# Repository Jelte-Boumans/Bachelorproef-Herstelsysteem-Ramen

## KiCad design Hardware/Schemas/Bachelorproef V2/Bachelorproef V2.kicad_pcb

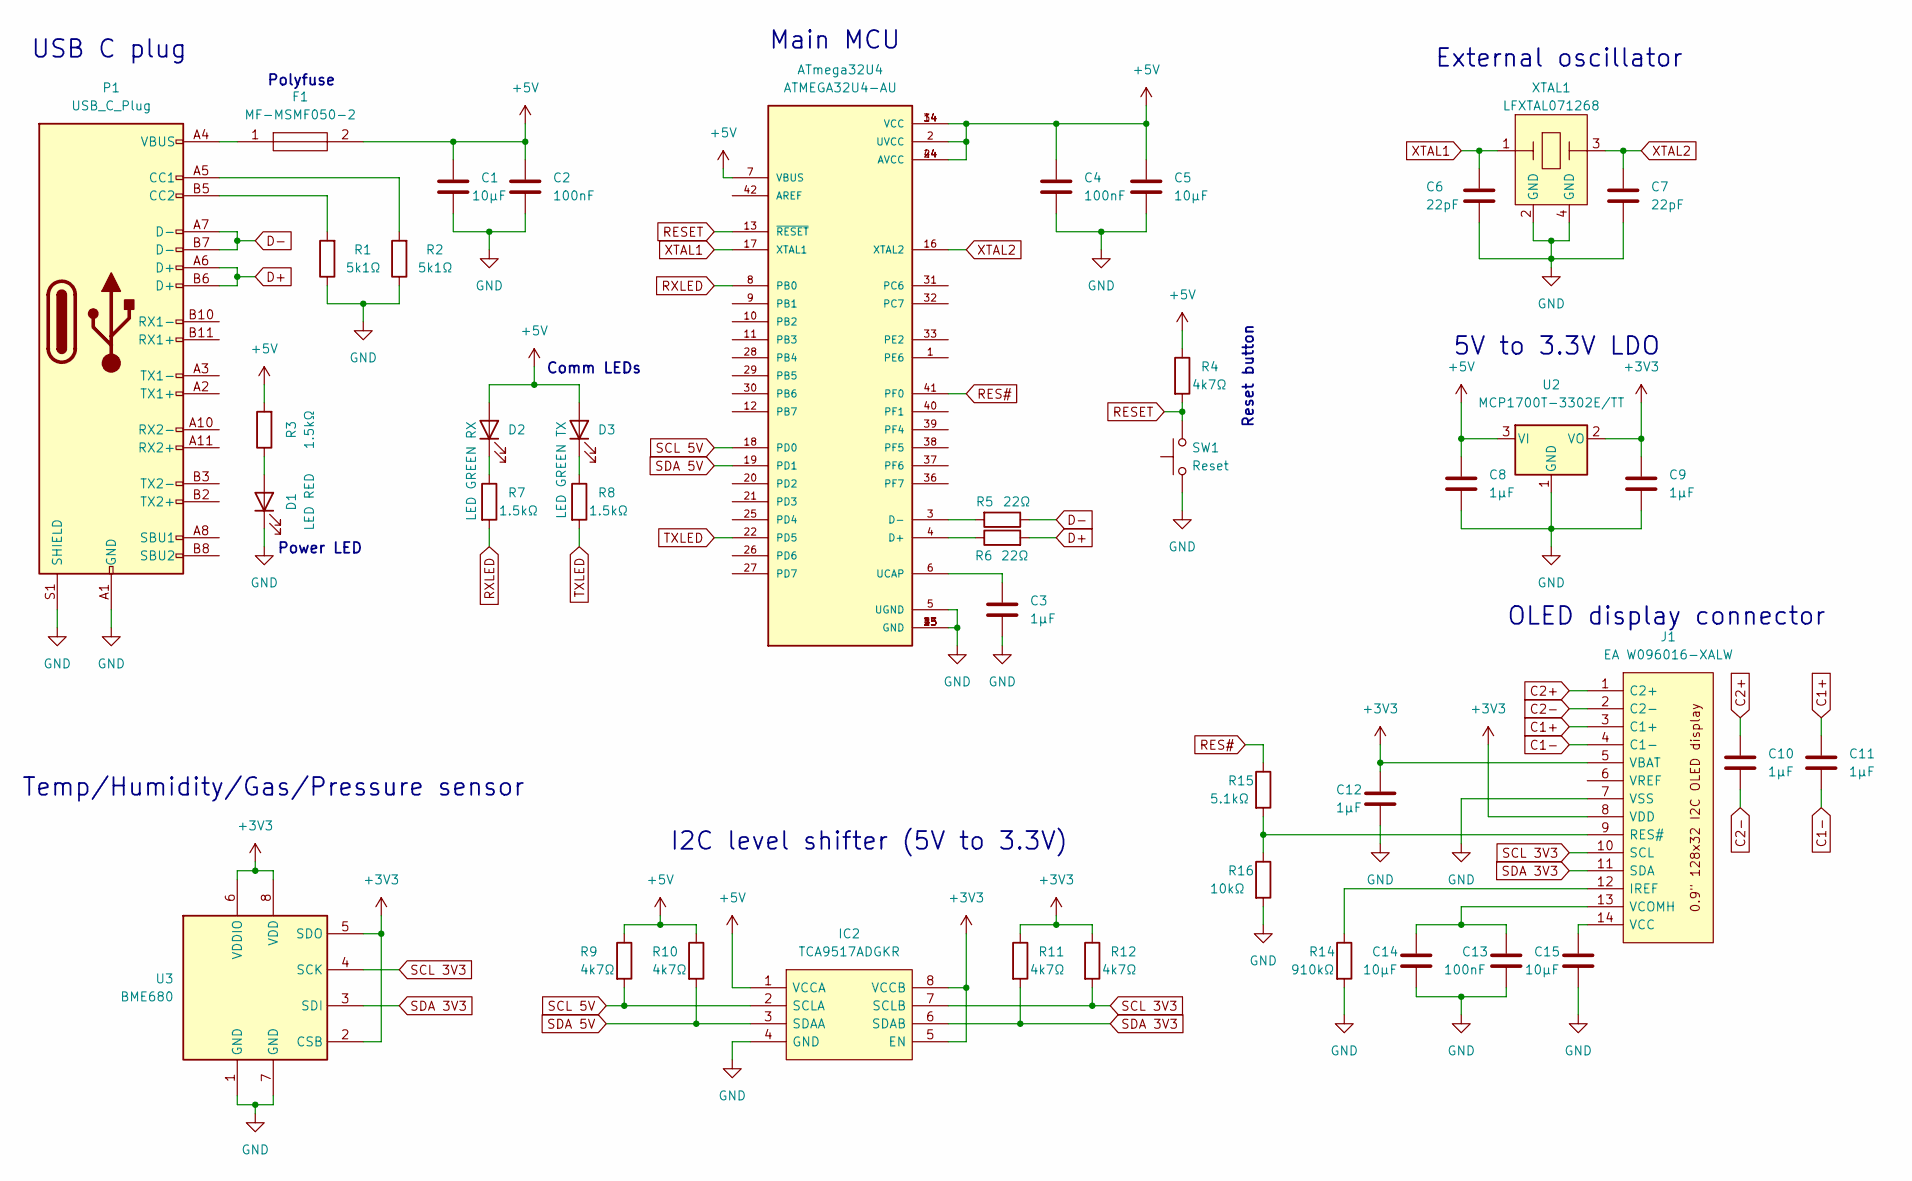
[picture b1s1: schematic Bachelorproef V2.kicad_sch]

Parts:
ATmega32U4: ATMEGA32U4-AU
C1, C5, C14, C15: 10µF; C_0603_1608Metric
C2, C4, C13: 100nF; C_0603_1608Metric
C3, C8, C9, C10, C11, C12: 1µF; C_0603_1608Metric
C6, C7: 22pF; C_0603_1608Metric
D1: LED RED; LED_0603_1608Metric_Pad1.05x0.95mm_HandSolder
D2: LED GREEN RX; LED_0603_1608Metric_Pad1.05x0.95mm_HandSolder
D3: LED GREEN TX; LED_0603_1608Metric_Pad1.05x0.95mm_HandSolder
F1: MF-MSMF050-2; Mouser Part Number 652-MF-MSMF050-2
IC2: TCA9517ADGKR
J1: EA W096016-XALW; EA_W096016-XALW
P1: USB_C_Plug; CX60-24S-UNIT
R1, R2: 5k1Ω; R_0603_1608Metric_Pad0.98x0.95mm_HandSolder
R3, R7, R8: 1.5kΩ; R_0603_1608Metric_Pad0.98x0.95mm_HandSolder
R4, R9, R10, R11, R12: 4k7Ω; R_0603_1608Metric_Pad0.98x0.95mm_HandSolder
R5, R6: 22Ω; R_0603_1608Metric_Pad0.98x0.95mm_HandSolder
R14: 910kΩ; R_0603_1608Metric_Pad0.98x0.95mm_HandSolder
R15: 5.1kΩ; R_0603_1608Metric_Pad0.98x0.95mm_HandSolder
R16: 10kΩ; R_0603_1608Metric_Pad0.98x0.95mm_HandSolder
SW1: Reset; SW_PTS636_SM43J_SMTR_LFS
U2: MCP1700T-3302E/TT; SOT-23
U3: BME680; Bosch_LGA-8_3x3mm_P0.8mm_ClockwisePinNumbering
XTAL1: LFXTAL071268

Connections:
+3V3: C9.1, C12.1, IC2.5 (EN), IC2.8 (VCCB), J1.5 (VBAT), J1.8 (VDD), R11.1, R12.1, U2.2 (VO), U3.2 (CSB), U3.5 (SDO), U3.6 (VDDIO), U3.8 (VDD)
+5V: ATmega32U4.2 (UVCC), ATmega32U4.7 (VBUS), ATmega32U4.14 (VCC), ATmega32U4.24 (AVCC), ATmega32U4.34 (VCC), ATmega32U4.44 (AVCC), C1.1, C2.1, C4.1, C5.1, C8.1, D2.2 (A), D3.2 (A), F1.2, IC2.1 (VCCA), R3.2, R4.1, R9.1, R10.1, U2.3 (VI)
C1+: C11.1, J1.3 (C1+)
C1-: C11.2, J1.4 (C1-)
C2+: C10.1, J1.1 (C2+)
C2-: C10.2, J1.2 (C2-)
D+: P1.A6 (D+), P1.B6 (D+), R6.2
D-: P1.A7 (D-), P1.B7 (D-), R5.1
GND: ATmega32U4.5 (UGND), ATmega32U4.15 (GND), ATmega32U4.23 (GND), ATmega32U4.35 (GND), ATmega32U4.43 (GND), C1.2, C2.2, C3.2, C4.2, C5.2, C6.2, C7.2, C8.2, C9.2, C12.2, C13.2, C14.2, C15.2, D1.1 (K), IC2.4 (GND), J1.7 (VSS), P1.A1 (GND), P1.A12 (GND), P1.B1 (GND), P1.B12 (GND), P1.S1 (SHIELD), R1.1, R2.1, R14.2, R16.2, SW1.1, U2.1 (GND), U3.1 (GND), U3.7 (GND), XTAL1.2 (GND), XTAL1.4 (GND)
unnamed: ATmega32U4.6 (UCAP), C3.1
unnamed: C13.1, C14.1, J1.13 (VCOMH)
unnamed: C15.1, J1.14 (VCC)
unnamed: D1.2 (A), R3.1
unnamed: D2.1 (K), R7.1
unnamed: D3.1 (K), R8.1
unnamed: F1.1, P1.A4 (VBUS), P1.A9 (VBUS), P1.B4 (VBUS), P1.B9 (VBUS)
unnamed: J1.9 (RES#), R15.2, R16.1
unnamed: J1.12 (IREF), R14.1
unnamed: P1.A5 (CC1), R2.2
unnamed: P1.B5 (CC2), R1.2
unnamed: ATmega32U4.3 (D-), R5.2
unnamed: ATmega32U4.4 (D+), R6.1
RES#: ATmega32U4.41 (PF0), R15.1
RESET: ATmega32U4.13 (~RESET), R4.2, SW1.2
RXLED: ATmega32U4.8 (PB0), R7.2
SCL 3V3: IC2.7 (SCLB), J1.10 (SCL), R12.2, U3.4 (SCK)
SCL 5V: ATmega32U4.18 (PD0), IC2.2 (SCLA), R9.2
SDA 3V3: IC2.6 (SDAB), J1.11 (SDA), R11.2, U3.3 (SDI)
SDA 5V: ATmega32U4.19 (PD1), IC2.3 (SDAA), R10.2
TXLED: ATmega32U4.22 (PD5), R8.2
XTAL1: ATmega32U4.17 (XTAL1), C6.1, XTAL1.1
XTAL2: ATmega32U4.16 (XTAL2), C7.1, XTAL1.3

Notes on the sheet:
Main MCU
Power LED
USB C plug
External oscillator
Reset button
I2C level shifter (5V to 3.3V)
Polyfuse
Temp/Humidity/Gas/Pressure sensor
OLED display connector
5V to 3.3V LDO
Comm LEDs

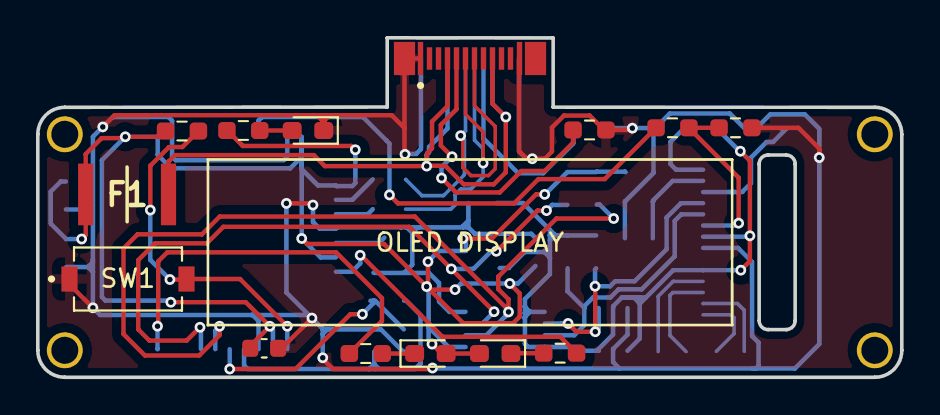
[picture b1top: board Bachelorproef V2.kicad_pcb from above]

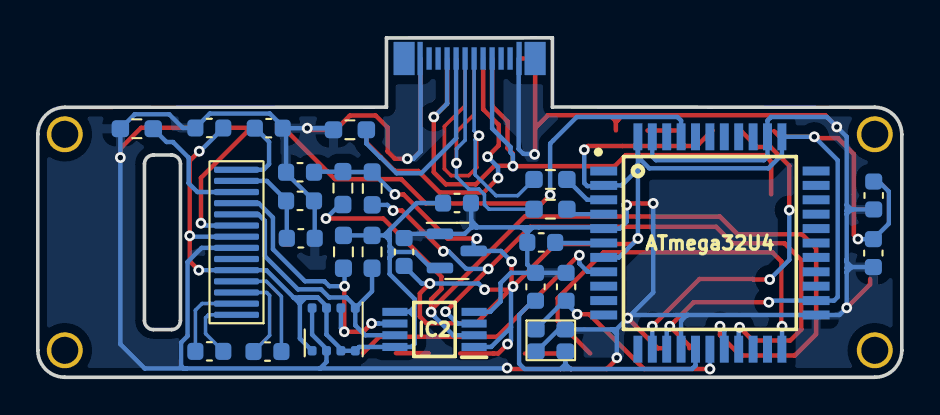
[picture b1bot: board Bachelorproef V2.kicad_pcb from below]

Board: 2 copper layers, 48.0 x 18.9 mm, 42 parts (28 on the bottom side), 32 nets.

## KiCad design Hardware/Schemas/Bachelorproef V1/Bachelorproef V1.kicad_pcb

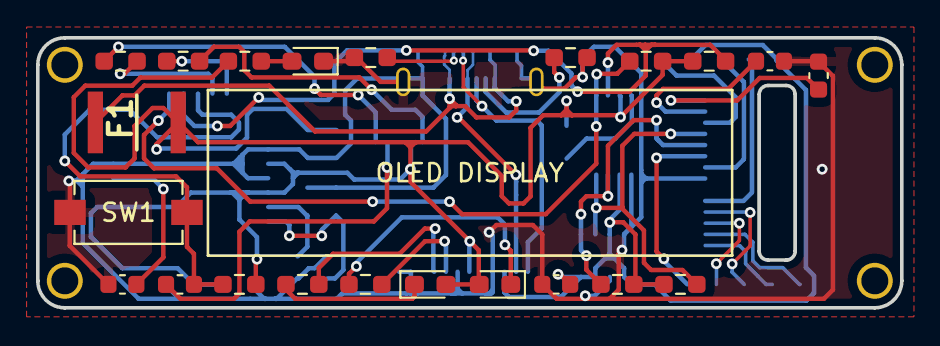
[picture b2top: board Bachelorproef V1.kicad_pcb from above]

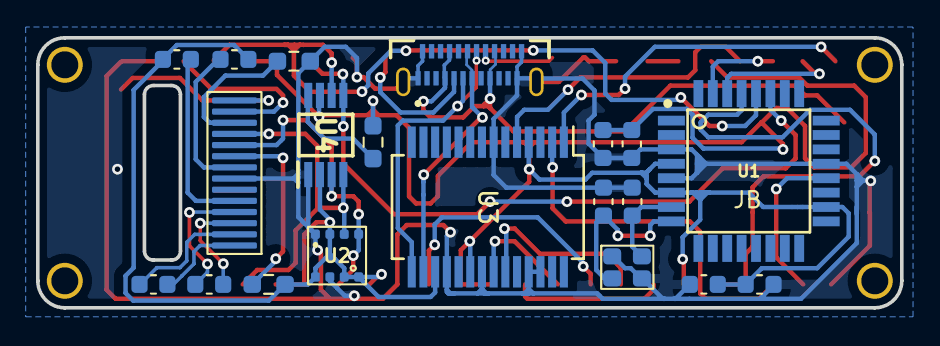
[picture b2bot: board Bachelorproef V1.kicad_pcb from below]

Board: 2 copper layers, 48.0 x 15.0 mm, 42 parts (20 on the bottom side), 37 nets.

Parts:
C1, C7, C10, C11, C12, C13: 1µF; C_0603_1608Metric
C2, C3, C4, C5, C6: 100nF; C_0603_1608Metric
C8, C9: 22pF; C_0603_1608Metric
C14, C15: 10µF; C_0603_1608Metric
D1: LED RED; LED_0603_1608Metric_Pad1.05x0.95mm_HandSolder
D2: LED GREEN RX; LED_0603_1608Metric_Pad1.05x0.95mm_HandSolder
D3: LED GREEN TX; LED_0603_1608Metric_Pad1.05x0.95mm_HandSolder
F1: MF-MSMF050-2
J1: EA W096016-XALW; EA_W096016-XALW
P1: USB_C_Plug; USB4155-03-C
R1: 150; R_0603_1608Metric_Pad0.98x0.95mm_HandSolder
R2, R3: 5K1; R_0603_1608Metric_Pad0.98x0.95mm_HandSolder
R4, R5: 1K; R_0603_1608Metric_Pad0.98x0.95mm_HandSolder
R6, R7: 120; R_0603_1608Metric_Pad0.98x0.95mm_HandSolder
R8, R9, R10, R11, R12: 4K7; R_0603_1608Metric_Pad0.98x0.95mm_HandSolder
R13, R15: 390K; R_0603_1608Metric_Pad0.98x0.95mm_HandSolder
R14: 10K; R_0603_1608Metric_Pad0.98x0.95mm_HandSolder
SW1: Reset; SW_PTS636_SM43J_SMTR_LFS
U1: ATMEGA328P-AU
U2: BME680; Bosch_LGA-8_3x3mm_P0.8mm_ClockwisePinNumbering
U3: FT232RL; SSOP-28_5.3x10.2mm_P0.65mm
U4: PI6ULS5V9306; TCA9517ADGKR
XTAL1: LFXTAL071268

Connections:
+3V3: C3.2, C12.1, C13.1, R11.1, R12.1, R14.1, U2.2 (CSB), U2.5 (SDO), U2.6 (VDDIO), U2.8 (VDD), U3.17 (3V3OUT), U4.2 (Vcc_A)
+5V: C1.1, C2.1, C6.1, C7.1, D2.2 (A), D3.2 (A), F1.2, R1.2, R8.1, R9.1, R10.1, R13.1, U1.4 (VCC), U1.6 (VCC), U1.18 (AVCC), U3.4 (VCCIO), U3.20 (VCC), U4.7 (Vcc_B)
C1+: C11.1, J1.3 (C1+)
C1-: C11.2, J1.4 (C1-)
C2+: C10.1, J1.1 (C2+)
C2-: C10.2, J1.2 (C2-)
D+: P1.A6 (D+), P1.B6 (D+), U3.15 (USBD+)
D-: P1.A7 (D-), P1.B7 (D-), U3.16 (USBD-)
GND: C1.2, C2.2, C3.1, C5.1, C6.2, C7.2, C8.2, C9.2, C14.2, C15.2, D1.1 (K), J1.7 (VSS), P1.A1 (GND), P1.A12 (GND), P1.B1 (GND), P1.B12 (GND), P1.S1 (SHIELD), R2.1, R3.1, R15.2, SW1.1, U1.3 (GND), U1.5 (GND), U1.21 (GND), U2.1 (GND), U2.7 (GND), U3.7 (GND), U3.18 (GND), U3.21 (GND), U3.25 (AGND), U3.26 (TEST), U4.1 (GND), XTAL1.2 (GND), XTAL1.4 (GND)
unnamed: C4.1, U3.2 (DTR)
unnamed: C5.2, U1.20 (AREF)
unnamed: C12.2, J1.8 (VDD)
unnamed: C13.2, J1.5 (VBAT)
unnamed: C14.1, J1.13 (VCOMH)
unnamed: C15.1, J1.14 (VCC)
unnamed: D1.2 (A), R1.1
unnamed: D2.1 (K), R6.1
unnamed: D3.1 (K), R7.1
unnamed: F1.1, P1.A4 (VBUS), P1.A9 (VBUS), P1.B4 (VBUS), P1.B9 (VBUS)
unnamed: J1.9 (RES#), R14.2
unnamed: J1.12 (IREF), R15.1
unnamed: P1.A5 (CC1), R3.2
unnamed: P1.B5 (CC2), R2.2
unnamed: R4.2, U3.1 (TXD)
unnamed: R5.2, U3.5 (RXD)
unnamed: R6.2, U3.23 (CBUS0)
unnamed: R7.2, U3.22 (CBUS1)
unnamed: R13.2, U4.8 (EN)
RESET: C4.2, R8.2, SW1.2, U1.29 (PC6/~RESET)
RX: R4.1, U1.30 (PD0)
SCL 3V3: J1.10 (SCL), R12.2, U2.4 (SCK), U4.3 (SCL_A)
SCL 5V: R9.2, U1.28 (PC5), U4.6 (SCL_A)
SDA 3V3: J1.11 (SDA), R11.2, U2.3 (SDI), U4.4 (SDA_A)
SDA 5V: R10.2, U1.27 (PC4), U4.5 (SDA_B)
TX: R5.1, U1.31 (PD1)
XTAL1: C8.1, U1.7 (PB6), XTAL1.1
XTAL2: C9.1, U1.8 (PB7), XTAL1.3
